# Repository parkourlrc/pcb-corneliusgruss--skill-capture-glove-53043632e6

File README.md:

# Skill-Capture Glove

*A worn skill-capture system — end-to-end hardware, SLAM, and policy. Solo, four months.*

An independent reimplementation of [Sunday Robotics'](https://sunday.ai/) Skill Capture Glove form factor, built solo from January through April 2026 as the final project for ME740 (Vision, Robotics, and Planning, Boston University). The hardware shown above is the V3 build with on-glove OV9782 stereo cameras; the production pose pipeline uses an externally-mounted GoPro Hero 10 plus [UMI's](https://umi-gripper.github.io/) monocular SLAM stack with [Hierarchical-Localization](https://github.com/cvg/Hierarchical-Localization) replacing ORB-SLAM3.

The repository contains every layer of the system: PCB design, firmware, capture pipeline, SLAM, alignment, and an ACT policy trained on 182 mug-on-coaster demonstrations.

<p align="center"><i>One demonstration: pick the mug, place it on the coaster (~15 s).</i></p>

---

## What's in here

| Layer | What it does | Where |
|---|---|---|
| **Hardware** | Custom DAQ PCB (KiCad), four MLX90393 Hall sensor PCBs, V3 glove CAD | [`hardware/`](hardware/) |
| **Firmware** | STM32G431 — bit-bang I²C, USB CDC, sensor scheduling | [`firmware/stm32_daq/`](firmware/stm32_daq/) |
| **Capture** | Master-tape recorder + GoPro offload + per-demo ingest | [`software/glove/capture/`](software/), [`software/glove/process/`](software/) |
| **SLAM** | HLoc (SuperPoint + LightGlue + NetVLAD + COLMAP) + pose-graph smoother + Gaussian σ=5 | [`software/glove/process/hloc/`](software/) |
| **Align** | Trajectory + proprioception → training-ready `episode.parquet` | [`software/glove/process/align.py`](software/) |
| **Policy** | ACT (Zhao et al. 2023) — DINOv2 frozen backbone, 23-D obs, 21-D action | [`software/glove/policy/`](software/) |
| **Review dashboard** | Browse-only FastAPI UI for triaging captured demos against quality metrics | [`software/glove/dashboard/`](software/glove/dashboard/) |
| **Paper** | ME740 final report | [`paper/me740_report.pdf`](paper/me740_report.pdf) |

---

## Pipeline

Five command-line stages, each operating on session directories with a stable schema:

```bash
python -m glove.capture record                     # continuous DAQ writer
python -m glove.capture offload                    # SD card → disk
python -m glove.process ingest --mp4 <file> ...    # MP4 + master tape → session dir
python -m glove.process build-model <map-session>  # SfM + HLoc map (run once per workspace)
python -m glove.process detect-aruco <map>         # tag detection
python -m glove.process calibrate-tag <map>        # gravity-align world frame
python -m glove.process localize <demo> --map <m>  # per-frame pose against the map
python -m glove.process align <demo>               # → episode.parquet
python -m glove.dashboard --data-dir data/sessions # browse + review demos at localhost:8000
```

See [`docs/reproduce.md`](docs/reproduce.md) for end-to-end reproduction commands. The full system architecture is documented in §3 of the [paper](paper/me740_report.pdf).

---

## Review dashboard

A FastAPI browse-only UI for triaging captured demonstrations. Surfaces per-demo trajectory-quality metrics (local-straightness, high-frequency RMS, pose-jump max) on a scrubbable timeline alongside the GoPro video. This is the tool that caught 23% of the unfiltered demonstration set as silent SLAM pose-graph re-anchoring artifacts during the label audit.

---

## Headline results

- **SLAM proven against ground truth.** A controlled validation against a Kalibr 6×6 AprilGrid places the production HLoc + σ=5 stack within **0.2 mm** of the absolute camera + PnP physical noise floor on static no-cup frames (HLoc 8.3 mm p95 vs. AprilGrid 8.1 mm p95). Further improvement bounded to capture-side hardware.
- **Per-joint Hall force sensing.** A controlled scale-press experiment recovers **+1.29 counts/g (R² = 0.64)** on the compliant 3F PIP joint — force enters the policy as a designed-in byproduct of the PIP-slit axial compliance, not via a calibrated load cell.
- **ACT policy on 182 demonstrations.** The production checkpoint reaches **28.8 mm position L1, 6.31° rotation L1, and 736 LSB Hall L1** on a held-out validation set against the HLoc + σ=5 ground truth — roughly 3.5× the truth-source's own measurement floor. A label-quality audit — driven by the [browse-only review dashboard](software/glove/dashboard/) shipped alongside the pipeline — excluded 23% of the unfiltered demonstration set as silent SLAM pose-graph re-anchoring artifacts before retraining.

  <p align="center"><i>Production policy predicting the next action chunk on a held-out demonstration. Predicted Hall traces (right panel) track the squeeze cycle through the grasp event.</i></p>

- **Eight-backend SLAM pivot chain.** DROID → COLMAP → custom stereo SIFT → OKVIS2 → custom GTSAM v1/v2/v3 → ORB-SLAM3 → HLoc + smoother. Each fork accepted what the evidence said rather than tuning a stack already at its diagnosed limit. Full chain documented in Sec. 5 of the paper.

---

## Built with

- [UMI](https://umi-gripper.github.io/) — Cheng Chi et al. 2024. Source of the Hero 10 + ORB-SLAM3 + Docker stack the production pipeline forked from.
- [Hierarchical-Localization (HLoc)](https://github.com/cvg/Hierarchical-Localization) — Sarlin et al. 2019. Production SLAM stack.
- [SuperPoint](https://github.com/magicleap/SuperPointPretrainedNetwork), [LightGlue](https://github.com/cvg/LightGlue), [NetVLAD](https://github.com/Relja/netvlad), [COLMAP](https://github.com/colmap/colmap)
- [ACT](https://github.com/tonyzhaozh/act) — Zhao et al. 2023. Policy architecture.
- [DINOv2](https://github.com/facebookresearch/dinov2) — frozen ViT-S/14 visual backbone.
- [GoPro Labs UTC precision-time QR](https://gopro.github.io/labs/control/precisiontime_utc/) — for ms-accurate camera-to-DAQ time sync.

---

## Hardware overview

- **Glove V3.** Two finger assemblies (single index + three-finger), four PIP and four MCP joints with 3 × 2 mm diametric magnets, fingertip caps, PIP axial-slit compliance.
- **DAQ PCB.** STM32G431 + TCA9548A I²C mux + QMI8658C IMU + 4 × MLX90393 Hall + 2 × VL53L1X ToF + USB CDC. Four-layer PCB, KiCad, manufactured by JLCPCB.
- **Cameras.** OV9782 stereo (on-glove, V3 build) + GoPro Hero 10 + MaxLens Mod 1.0 (155° fisheye, externally mounted, used for production SLAM).

The on-glove OV9782 stereo cameras shown in the hero image were the original SLAM sensors. The current pose pipeline uses the externally-mounted GoPro because OV9782 stereo VIO did not converge on the assembled glove (finger occlusion + USB bandwidth). Whether the HLoc stack would close the loop on the OV9782 cameras given a V4 USB and lens revision is an open question.

---

## Paper

**[A Worn Skill-Capture System: End-to-End Hardware, SLAM, and Policy](paper/me740_report.pdf)**
Cornelius Gruss · ME740 (Vision, Robotics, and Planning) · Boston University · 2026

---

## License

[MIT](LICENSE) — use, modify, and redistribute freely.

## Acknowledgments

Form factor inspired by [Sunday Robotics'](https://sunday.ai/) Skill Capture Glove. SLAM pipeline forked from [UMI](https://umi-gripper.github.io/). Policy architecture adapted from [ALOHA / ACT](https://github.com/tonyzhaozh/act). Built as the final project for ME740 (Spring 2026, Boston University) under Prof. John Baillieul.

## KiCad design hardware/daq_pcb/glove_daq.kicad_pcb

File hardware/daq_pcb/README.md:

# DAQ PCB

Sensor aggregation and timing backbone for the glove. Streams synchronized proprioceptive data over USB-CDC to the host.

| | |
|---|---|
| **MCU** | STM32G431CBT6 (LQFP-48, 170 MHz, crystal-less USB via CRS) |
| **IMU** | QMI8658C — 6-DoF, I²C @ 0x6A |
| **I²C mux** | TCA9548A @ 0x70 — 6 sensor channels |
| **Sensors (off-board)** | 4× MLX90393 Hall (joint), 2× VL53L1X ToF |
| **Camera sync** | TIM1 hardware PWM, 30 Hz, 3.3 V on JST-SH |
| **Host link** | USB-C, CDC-ACM @ 12 Mbps |
| **Stack-up** | 2-layer FR4, 1.6 mm, HASL |
| **Form factor** | ~40 × 30 mm |
| **Fabricator** | JLCPCB (PCB + economic SMT assembly) |

## Files

| Path | What |
|---|---|
| `glove_daq.kicad_pro` / `.kicad_pcb` / `.kicad_sch` | KiCad 7 project |
| `glove_daq.pdf` | Schematic export |
| `glove_daq.step` | 3D model (board + components) |
| `BOM.xlsx` | Bill of materials |
| `JLCPCB_BOM.csv` | JLC-formatted BOM for SMT assembly |
| `mfr/glove_daq.zip` | Gerber + drill bundle (drop into JLCPCB upload) |
| `mfr/glove_daq-all-pos.csv` | Component positions for SMT assembly |
| `aruco/` | ArUco marker footprints + reference renders |

## Manufacturing

Upload `mfr/glove_daq.zip` (gerbers + drill) and `mfr/glove_daq-all-pos.csv` (positions) plus `JLCPCB_BOM.csv` to JLCPCB's PCBA flow. SWD header (J2, 1×4 2.54 mm THT) is hand-soldered.

## I²C mux assignment

| Channel | Sensor | Address |
|---|---|---|
| CH0 | VL53L1X ToF (bottom) | 0x29 |
| CH1 | MLX90393 Hall (3F MCP) | 0x0C |
| CH2 | MLX90393 Hall (Index PIP) | 0x0C |
| CH3 | MLX90393 Hall (3F PIP) | 0x0C |
| CH4 | MLX90393 Hall (Index MCP) | 0x0C |
| CH5 | VL53L1X ToF (top) | 0x29 |

## USB packet format (40 bytes, type 0x02 @ 30 Hz)

| Offset | Size | Field |
|---|---|---|
| 0 | 1 | Packet type (0x02) |
| 1 | 4 | Timestamp (ns) |
| 5 | 24 | 4× Hall (Bx, By, Bz int16) |
| 29 | 4 | 2× ToF (mm, int16; −1 = no reading) |
| 33 | 4 | Sync pulse timestamp (µs of last camera trigger) |
| 37 | 1 | Status flags |
| 38 | 2 | Sync sequence counter |

A separate type-0x01 packet streams raw IMU at ~680 Hz.

## Design notes

- **Crystal-less USB.** STM32G4's Clock Recovery System trims HSI48 against USB SOF — eliminates the external crystal, removes a failure mode, frees board area. Init order matters: enable HSI48 → enable CRS → select HSI48 as USB clock → init USB peripheral.
- **No battery, no SD card.** Tethered operation is required for video offload anyway, so battery + power-path management would add ~10 components for no functional gain. SPI2 (PB12–PB15) is left free for future logging.
- **JST-SH (1.0 mm) connectors.** Same physical footprint as Qwiic / STEMMA QT, half the area of JST-PH. SMD right-angle variants keep the board flat for IMU rigidity.
- **IMU substitution.** JLCPCB's "ICM-42688-PC" extended part (C2839811) is a pin-compatible **clone** — the actual silicon is QMI8658C, with a different register map and I²C-only operation. Firmware bit-bangs I²C on the SPI1 pads (PA5/SCK→SCL, PA7/MOSI→SDA, PA4/CS held HIGH for I²C mode). Lesson: never use JLC "extended" parts for specialty ICs without verifying WHO_AM_I.
- **Bit-bang I²C everywhere.** STM32 HAL's I²C peripheral hung intermittently under sensor load (mux switching + clock stretching). Bit-banging is slower but deterministic.

## License

MIT — see repository root.

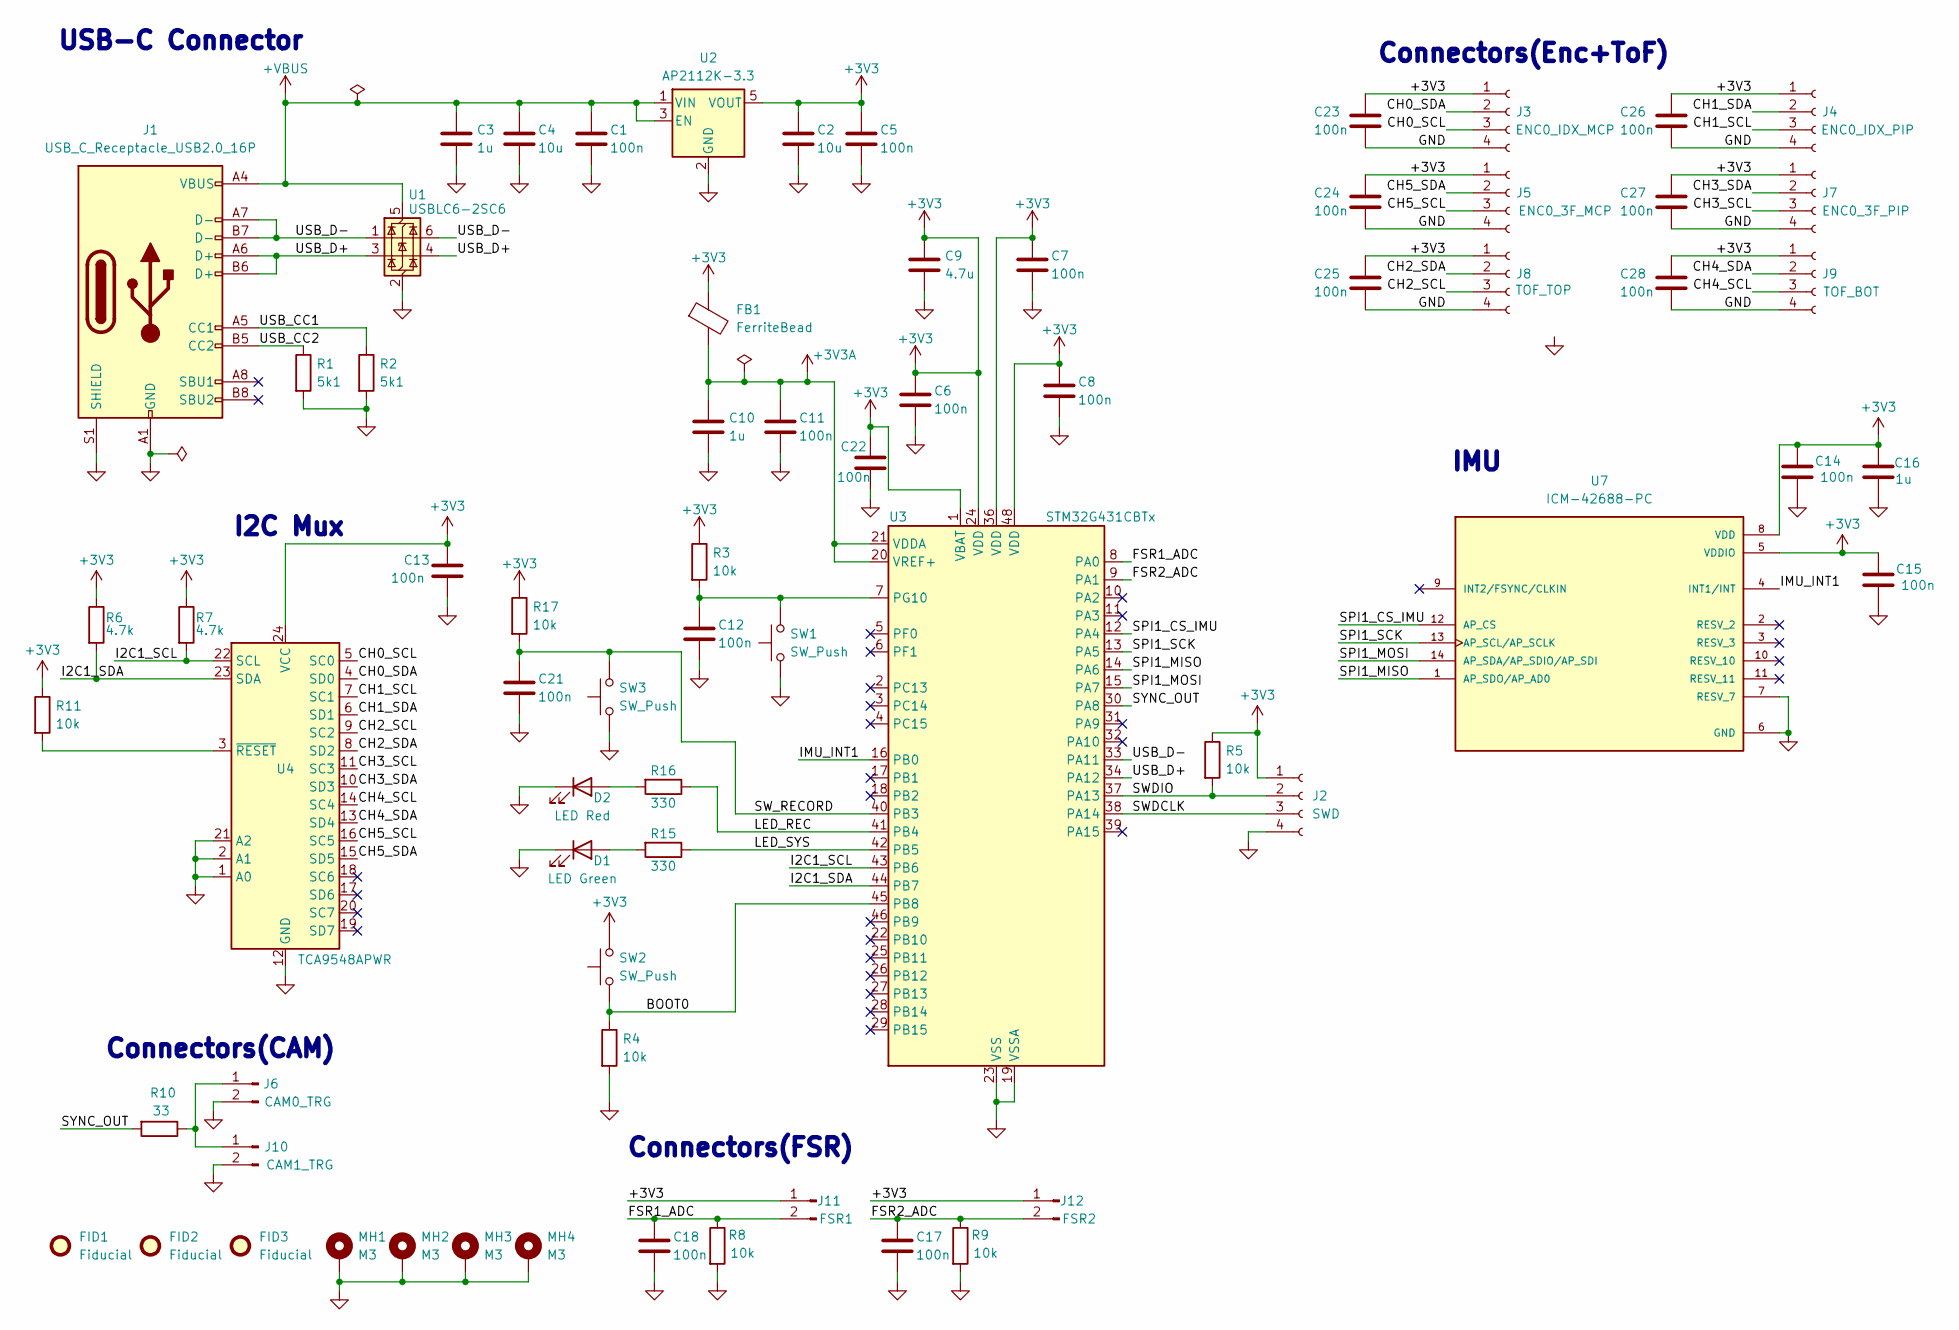
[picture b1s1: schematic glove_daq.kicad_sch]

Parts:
C1, C5, C6, C7, C8, C11, C12, C13, C14, C15, C17, C18, C21, C22, C23, C24, C25, C26, C27, C28: 100n; C_0402_1005Metric; LCSC C307331
C2, C4: 10u; C_0402_1005Metric; LCSC C15525
C3, C10, C16: 1u; C_0402_1005Metric; LCSC C52923
C9: 4.7u; C_0402_1005Metric; LCSC C23733
D1: LED Green; LED_0805_2012Metric; LCSC C2297
D2: LED Red; LED_0603_1608Metric; LCSC C2286
FB1: FerriteBead; L_0603_1608Metric; LCSC C1002
FID1, FID2, FID3: Fiducial; Fiducial_1mm_Mask2mm
J1: USB_C_Receptacle_USB2.0_16P; USB_C_Receptacle_GCT_USB4105-xx-A_16P_TopMnt_Horizontal; LCSC C3020560
J2: SWD; JST_SH_BM04B-SRSS-TB_1x04-1MP_P1.00mm_Vertical; LCSC C160390
J3: ENC0_IDX_MCP; JST_SH_SM04B-SRSS-TB_1x04-1MP_P1.00mm_Horizontal; LCSC C160404
J4: ENC0_IDX_PIP; JST_SH_SM04B-SRSS-TB_1x04-1MP_P1.00mm_Horizontal; LCSC C160404
J5: ENC0_3F_MCP; JST_SH_SM04B-SRSS-TB_1x04-1MP_P1.00mm_Horizontal; LCSC C160404
J6: CAM0_TRG; JST_SH_SM02B-SRSS-TB_1x02-1MP_P1.00mm_Horizontal; LCSC C160402
J7: ENC0_3F_PIP; JST_SH_SM04B-SRSS-TB_1x04-1MP_P1.00mm_Horizontal; LCSC C160404
J8: TOF_TOP; JST_SH_SM04B-SRSS-TB_1x04-1MP_P1.00mm_Horizontal; LCSC C160404
J9: TOF_BOT; JST_SH_SM04B-SRSS-TB_1x04-1MP_P1.00mm_Horizontal; LCSC C160404
J10: CAM1_TRG; JST_SH_SM02B-SRSS-TB_1x02-1MP_P1.00mm_Horizontal; LCSC C160402
J11: FSR1; JST_SH_SM02B-SRSS-TB_1x02-1MP_P1.00mm_Horizontal; LCSC C160402
J12: FSR2; JST_SH_SM02B-SRSS-TB_1x02-1MP_P1.00mm_Horizontal; LCSC C160402
MH1, MH2, MH3, MH4: M3; MountingHole_3.2mm_M3_Pad
R1, R2: 5k1; R_0402_1005Metric; LCSC C25905
R3, R4, R5, R8, R9, R11, R17: 10k; R_0402_1005Metric; LCSC C25744
R6, R7: 4.7k; R_0402_1005Metric; LCSC C25900
R10: 33; R_0402_1005Metric; LCSC C25105
R15, R16: 330; R_0402_1005Metric; LCSC C25104
SW1, SW2, SW3: SW_Push; SW_SPST_TS-1088-xR025; LCSC C720477
U1: USBLC6-2SC6; SOT-23-6; LCSC C7519
U2: AP2112K-3.3; SOT-23-5; LCSC C51118
U3: STM32G431CBTx; LQFP-48_7x7mm_P0.5mm; LCSC C529355
U4: TCA9548APWR; TSSOP-24_4.4x7.8mm_P0.65mm; LCSC C130026
U7: ICM-42688-PC; PQFN50P300X250X97-14N; PARTREV 1.2; LCSC C48586483

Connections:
+3V3: C2.1, C5.1, C6.1, C7.1, C8.1, C9.1, C13.1, C14.1, C15.1, C16.1, C22.1, C23.1, C24.1, C25.1, C26.1, C27.1, C28.1, FB1.1, J2.1, J3.1, J4.1, J5.1, J7.1, J8.1, J9.1, J11.1, J12.1, R3.1, R5.1, R6.1, R7.1, R11.1, R17.1, SW2.2, U2.5 (VOUT), U3.1 (VBAT), U3.24 (VDD), U3.36 (VDD), U3.48 (VDD), U4.24 (VCC), U7.5 (VDDIO), U7.8 (VDD)
+3V3A: C10.1, C11.1, FB1.2, U3.20 (VREF+), U3.21 (VDDA)
+VBUS: C1.1, C3.1, C4.1, J1.A4 (VBUS), J1.A9 (VBUS), J1.B4 (VBUS), J1.B9 (VBUS), U1.5 (VBUS), U2.1 (VIN), U2.3 (EN)
/BOOT0: R4.1, SW2.1, U3.45 (PB8)
/CH0_SCL: J3.3, U4.5 (SC0)
/CH0_SDA: J3.2, U4.4 (SD0)
/CH1_SCL: J4.3, U4.7 (SC1)
/CH1_SDA: J4.2, U4.6 (SD1)
/CH2_SCL: J8.3, U4.9 (SC2)
/CH2_SDA: J8.2, U4.8 (SD2)
/CH3_SCL: J7.3, U4.11 (SC3)
/CH3_SDA: J7.2, U4.10 (SD3)
/CH4_SCL: J9.3, U4.14 (SC4)
/CH4_SDA: J9.2, U4.13 (SD4)
/CH5_SCL: J5.3, U4.16 (SC5)
/CH5_SDA: J5.2, U4.15 (SD5)
/FSR1_ADC: C18.1, J11.2, R8.1, U3.8 (PA0)
/FSR2_ADC: C17.1, J12.2, R9.1, U3.9 (PA1)
/I2C1_SCL: R7.2, U3.43 (PB6), U4.22 (SCL)
/I2C1_SDA: R6.2, U3.44 (PB7), U4.23 (SDA)
/IMU_INT1: U3.16 (PB0), U7.4 (INT1/INT)
/LED_REC: R16.1, U3.41 (PB4)
/LED_SYS: R15.1, U3.42 (PB5)
/SPI1_CS_IMU: U3.12 (PA4), U7.12 (AP_CS)
/SPI1_MISO: U3.14 (PA6), U7.1 (AP_SDO/AP_AD0)
/SPI1_MOSI: U3.15 (PA7), U7.14 (AP_SDA/AP_SDIO/AP_SDI)
/SPI1_SCK: U3.13 (PA5), U7.13 (AP_SCL/AP_SCLK)
/SWDCLK: J2.3, U3.38 (PA14)
/SWDIO: J2.2, R5.2, U3.37 (PA13)
/SW_RECORD: C21.1, R17.2, SW3.2, U3.40 (PB3)
/SYNC_OUT: R10.2, U3.30 (PA8)
/USB_CC1: J1.A5 (CC1), R2.1
/USB_CC2: J1.B5 (CC2), R1.1
/USB_D+: J1.A6 (D+), J1.B6 (D+), U1.3 (I/O2), U1.4 (I/O2), U3.34 (PA12)
/USB_D-: J1.A7 (D-), J1.B7 (D-), U1.1 (I/O1), U1.6 (I/O1), U3.33 (PA11)
GND: C1.2, C2.2, C3.2, C4.2, C5.2, C6.2, C7.2, C8.2, C9.2, C10.2, C11.2, C12.2, C13.2, C14.2, C15.2, C16.2, C17.2, C18.2, C21.2, C22.2, C23.2, C24.2, C25.2, C26.2, C27.2, C28.2, D1.1 (K), D2.1 (K), J1.A1 (GND), J1.A12 (GND), J1.B1 (GND), J1.B12 (GND), J1.S1 (SHIELD), J2.4, J3.4, J4.4, J5.4, J6.2, J7.4, J8.4, J9.4, J10.2, MH1.1, MH2.1, MH3.1, MH4.1, R1.2, R2.2, R4.2, R8.2, R9.2, SW1.1, SW3.1, U1.2 (GND), U2.2 (GND), U3.19 (VSSA), U3.23 (VSS), U3.35 (VSS), U3.47 (VSS), U4.1 (A0), U4.2 (A1), U4.12 (GND), U4.21 (A2), U7.6 (GND), U7.7 (RESV_7)
unnamed: D1.2 (A), R15.2
unnamed: D2.2 (A), R16.2
unnamed: J6.1, J10.1, R10.1
unnamed: C12.1, R3.2, SW1.2, U3.7 (PG10)
unnamed: R11.2, U4.3 (~RESET)

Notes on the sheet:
USB-C Connector
Connectors(CAM)
Connectors(FSR)
IMU
I2C Mux
Connectors(Enc+ToF)

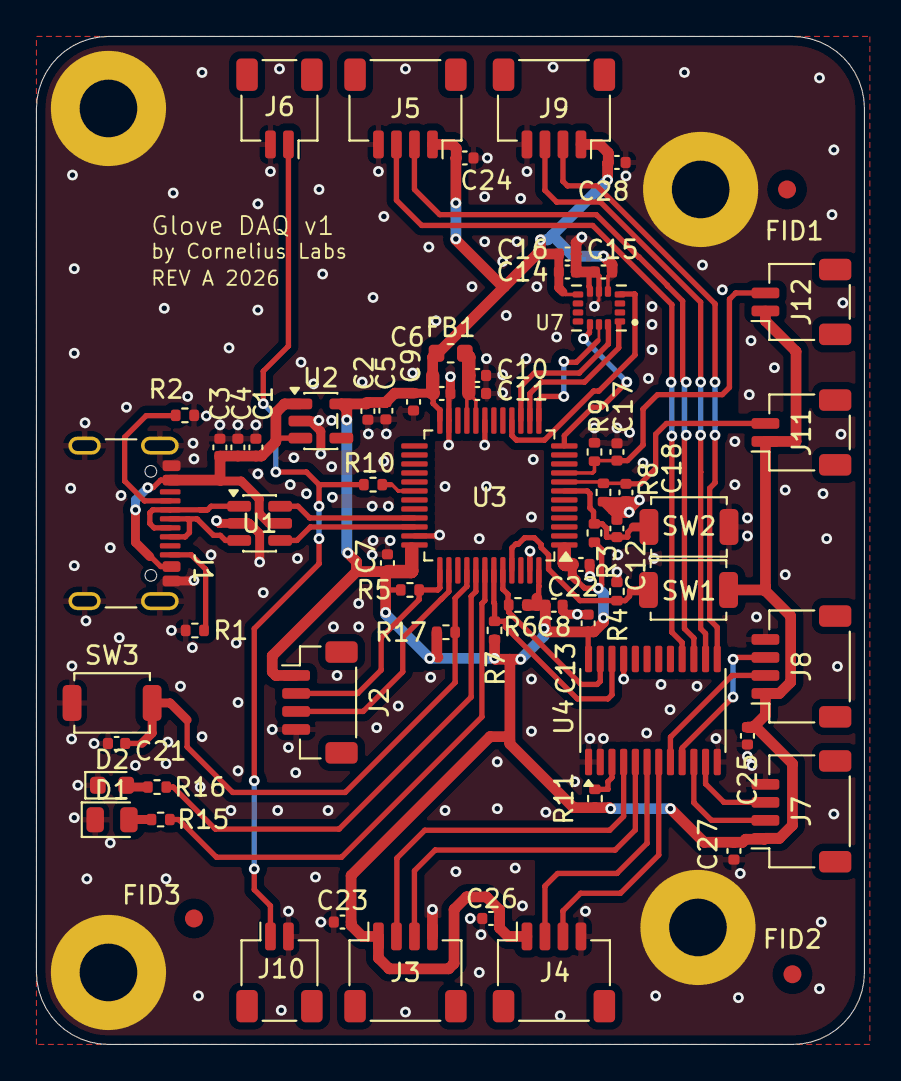
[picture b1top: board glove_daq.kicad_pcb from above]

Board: 2 copper layers, 46.0 x 56.0 mm, 70 parts (0 on the bottom side), 41 nets.

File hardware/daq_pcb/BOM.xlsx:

Ref | Value | Description | Package | LCSC Part # | JLCPCB Type | Group | Qty | Notes
USB-C + Power
J1 | USB_C_16P | USB-C 2.0 Receptacle 16-pin | SMD | C165948 | Basic |  | 1 | HRO TYPE-C-31-M-12
U1 | USBLC6-2SC6 | USB ESD Protection | SOT-23-6 | C7519 | Basic |  | 1
R1 | 5.1kΩ | CC1 pull-down | 0402 | C25905 | Basic |  | 1
R2 | 5.1kΩ | CC2 pull-down | 0402 | C25905 | Basic |  | 1
C1 | 100nF | VBUS HF decoupling | 0402 | C307331 | Basic |  | 1 | 50V rated
C3 | 1µF | VBUS mid-freq decoupling | 0402 | C52923 | Basic |  | 1
C4 | 10µF | VBUS bulk decoupling | 0402 | C15525 | Basic |  | 1 | 16V rated
U2 | AP2112K-3.3 | 3.3V LDO 600mA | SOT-23-5 | C51118 | Basic |  | 1
C2 | 10µF | LDO output bulk | 0402 | C15525 | Basic |  | 1
C5 | 100nF | LDO output HF | 0402 | C307331 | Basic |  | 1
STM32G431 MCU
U3 | STM32G431CBT6 | ARM Cortex-M4 MCU 170MHz | LQFP-48 | C529331 | Extended |  | 1 | Crystal-less USB via CRS
C6 | 100nF | VDD decoupling (pin 24) | 0402 | C307331 | Basic |  | 1
C7 | 100nF | VDD decoupling (pin 36) | 0402 | C307331 | Basic |  | 1
C8 | 100nF | VDD decoupling (pin 48) | 0402 | C307331 | Basic |  | 1
C9 | 4.7µF | VDD bulk | 0402 | C23733 | Basic |  | 1
C22 | 100nF | VBAT decoupling | 0402 | C307331 | Basic |  | 1
FB1 | 600Ω@100MHz | VDDA ferrite bead filter | 0402 | C281128 | Basic |  | 1
C10 | 1µF | VDDA decoupling | 0402 | C52923 | Basic |  | 1
C11 | 100nF | VDDA HF decoupling | 0402 | C307331 | Basic |  | 1
R17 | 10kΩ | NRST pull-up | 0402 | C25744 | Basic |  | 1
C12 | 100nF | NRST filter cap | 0402 | C307331 | Basic |  | 1
SW1 | RESET | Tactile push button | 6x6mm SMD | C318884 | Basic |  | 1
R4 | 10kΩ | BOOT0 pull-down | 0402 | C25744 | Basic |  | 1
SW2 | BOOT0 | Tactile push button | 6x6mm SMD | C318884 | Basic |  | 1
J2 | SWD Header | 1x4 pin header 2.54mm | THT | C2337 | Basic |  | 1
R5 | 10kΩ | SWDIO pull-up | 0402 | C25744 | Basic |  | 1
Camera Sync
R10 | 33Ω | SYNC_OUT series damping | 0402 | C25105 | Basic |  | 1
J6 | CAM0_TRG | JST-PH 2-pin right-angle | SMD | C131337 | Basic |  | 1
J10 | CAM1_TRG | JST-PH 2-pin right-angle | SMD | C131337 | Basic |  | 1
I2C Mux + Sensors
U4 | TCA9548APWR | I2C 8-channel multiplexer | TSSOP-24 | C130026 | Basic |  | 1
C13 | 100nF | Mux VCC decoupling | 0402 | C307331 | Basic |  | 1
R11 | 10kΩ | Mux RESET pull-up | 0402 | C25744 | Basic |  | 1
R6 | 4.7kΩ | I2C SCL pull-up | 0402 | C25900 | Basic |  | 1
R7 | 4.7kΩ | I2C SDA pull-up | 0402 | C25900 | Basic |  | 1
J3 | ENC0_IDX_MCP | JST-PH 4-pin right-angle | SMD | C131337 | Basic |  | 1 | Encoder CH0
J4 | ENC0_IDX_PIP | JST-PH 4-pin right-angle | SMD | C131337 | Basic |  | 1 | Encoder CH1
J5 | ENC0_3F_MCP | JST-PH 4-pin right-angle | SMD | C131337 | Basic |  | 1 | Encoder CH2
J7 | ENC0_3F_PIP | JST-PH 4-pin right-angle | SMD | C131337 | Basic |  | 1 | Encoder CH3
J8 | TOF_TOP | JST-PH 4-pin right-angle | SMD | C131337 | Basic |  | 1 | ToF CH4
J9 | TOF_BOT | JST-PH 4-pin right-angle | SMD | C131337 | Basic |  | 1 | ToF CH5
C_J3 | 100nF | ENC0_IDX_MCP connector decoupling | 0402 | C307331 | Basic |  | 1
C_J4 | 100nF | ENC0_IDX_PIP connector decoupling | 0402 | C307331 | Basic |  | 1
C_J5 | 100nF | ENC0_3F_MCP connector decoupling | 0402 | C307331 | Basic |  | 1
C_J7 | 100nF | ENC0_3F_PIP connector decoupling | 0402 | C307331 | Basic |  | 1
C_J8 | 100nF | TOF_TOP connector decoupling | 0402 | C307331 | Basic |  | 1
C_J9 | 100nF | TOF_BOT connector decoupling | 0402 | C307331 | Basic |  | 1
IMU
U7 | ICM-42688-P | 6-axis IMU (gyro+accel) | LGA-14 | C2839811 | Extended |  | 1 | Check stock — ICM-42670-P as backup
C14 | 100nF | IMU VDDIO decoupling | 0402 | C307331 | Basic |  | 1
C15 | 100nF | IMU VDD decoupling | 0402 | C307331 | Basic |  | 1
C16 | 1µF | IMU VDD bulk | 0402 | C52923 | Basic |  | 1
FSR Force Sensing
J11 | FSR1 | JST-PH 2-pin right-angle | SMD | C131337 | Basic |  | 1
J12 | FSR2 | JST-PH 2-pin right-angle | SMD | C131337 | Basic |  | 1
R8 | 10kΩ | FSR1 pull-down | 0402 | C25744 | Basic |  | 1
R9 | 10kΩ | FSR2 pull-down | 0402 | C25744 | Basic |  | 1
C17 | 100nF | FSR1 RC filter | 0402 | C307331 | Basic |  | 1
C18 | 100nF | FSR2 RC filter | 0402 | C307331 | Basic |  | 1
SD Card
J13 | Micro_SD | MicroSD card socket push-push | SMD | C91145 | Basic |  | 1 | HYC80-TF09-375 or equiv
R12 | 10kΩ | SD DAT2 pull-up | 0402 | C25744 | Basic |  | 1
R13 | 10kΩ | SD DAT1 pull-up | 0402 | C25744 | Basic |  | 1
R14 | 10kΩ | SD Card Detect pull-up | 0402 | C25744 | Basic |  | 1
C19 | 10µF | SD VDD bulk | 0402 | C15525 | Basic |  | 1
C20 | 100nF | SD VDD HF | 0402 | C307331 | Basic |  | 1
User Interface
D1 | Green LED | System status LED | 0402 | C2297 | Basic |  | 1
D2 | Red LED | Recording status LED | 0402 | C2286 | Basic |  | 1
R15 | 330Ω | Green LED current limit | 0402 | C25104 | Basic |  | 1
R16 | 330Ω | Red LED current limit | 0402 | C25104 | Basic |  | 1
SW3 | RECORD | Tactile push button | 6x6mm SMD | C318884 | Basic |  | 1
R3 | 10kΩ | Record button pull-up | 0402 | C25744 | Basic |  | 1
C21 | 100nF | Record button debounce | 0402 | C307331 | Basic |  | 1
Mechanical
MH1-4 | M3 | Mounting hole pad | M3 THT | — | — |  | 4 | Connect pad to GND
FID1-3 | Fiducial | 1mm copper, 2mm mask opening | Fiducial | — | — |  | 3 | JLCPCB pick-and-place alignment
BOM Summary
Total Unique Parts | ~30
Total Component Count | ~72
JLCPCB Basic Parts | ~28
JLCPCB Extended Parts | 2 (STM32G431, ICM-42688-P)
Passive Size | 0402 (all)
Board Layers | 2 (recommended)

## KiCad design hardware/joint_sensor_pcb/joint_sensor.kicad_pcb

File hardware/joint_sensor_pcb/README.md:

# Joint sensor PCB

Micro-PCB that mounts on each finger flexure to capture joint angle and axial compliance from a single diametric magnet.

| | |
|---|---|
| **Sensor** | Melexis MLX90393 (3-axis Hall, QFN-16) |
| **Interface** | I²C @ 0x0C (routed through DAQ board's TCA9548A mux) |
| **Power** | 3.3 V from DAQ board |
| **Form factor** | 15 × 20 mm, 2-layer FR4 |
| **Connector** | JST-SH 4-pin right-angle (3V3 / GND / SDA / SCL) |
| **Magnet** | 3 × 2 mm N52 diametric, mounted in finger CAD |
| **Quantity per glove** | 4 (Index MCP + PIP, three-finger MCP + PIP) |

## Files

| Path | What |
|---|---|
| `joint_sensor.kicad_pro` / `.kicad_pcb` / `.kicad_sch` | KiCad 7 project |
| `joint_sensor.step` | 3D model |
| `mfr/joint_sensor.zip` | Gerber + drill bundle |
| `mfr/joint_sensor-all-pos.csv` | Component positions for SMT |

## What it produces

Three int16 readings per sensor (Bx, By, Bz). The host derives:

- **Angle** from `atan2(By, Bx)` — continuous through wrap, no discontinuity.
- **Force** from `Bz` magnitude — the axial-slit PIP flexure deflects under load, changing the magnet's standoff and shifting Bz. Calibrated against a precision scale: **+1.29 counts/g, R² = 0.64** on the compliant 3F PIP joint (range ~300–1300 g).

The policy receives raw `(Bx, By, Bz)` per sensor — no on-host atan2 — so the network sees angle and force as a single 12-D continuous representation.

## Layout rules

1. **Sensor on the centerline**, aligned with the hinge-pin axis in CAD.
2. **No copper under the chip** — solid pours induce eddy currents under a moving magnet that bias the field reading. KiCad keep-out zone, ~5 × 5 mm, both layers.
3. **15 mm lever arm** between the sensor center and the M2 mounting holes. The flexure deflection that gives Bz its force-sensing range scales with this distance.

## License

MIT — see repository root.

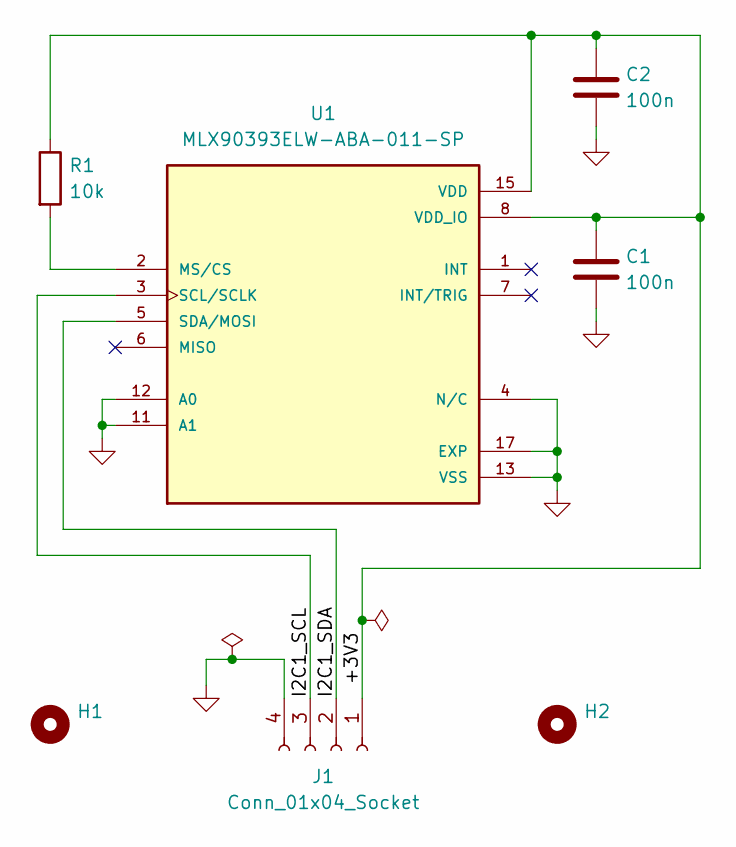
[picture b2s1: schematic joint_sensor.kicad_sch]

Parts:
C1, C2: 100n; C_0402_1005Metric; LCSC C307331
H1, H2: MountingHole; MountingHole_2.2mm_M2_DIN965
J1: Conn_01x04_Socket; JST_SH_SM04B-SRSS-TB_1x04-1MP_P1.00mm_Horizontal; LCSC C160404
R1: 10k; R_0402_1005Metric; LCSC C25744
U1: MLX90393ELW-ABA-011-SP; QFN50P300X300X100-17N; PARTREV 010; LCSC C2649492

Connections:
/+3V3: C1.1, C2.1, J1.1, R1.1, U1.8 (VDD_IO), U1.15 (VDD)
/I2C1_SCL: J1.3, U1.3 (SCL/SCLK)
/I2C1_SDA: J1.2, U1.5 (SDA/MOSI)
GND: C1.2, C2.2, J1.4, U1.4 (N/C), U1.9 (N/C), U1.10 (N/C), U1.11 (A1), U1.12 (A0), U1.13 (VSS), U1.14 (N/C), U1.16 (N/C), U1.17 (EXP)
unnamed: R1.2, U1.2 (MS/CS)

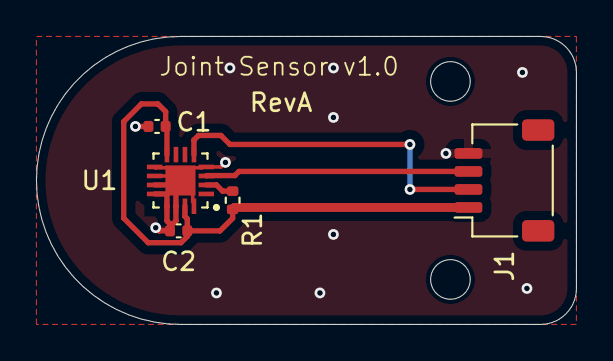
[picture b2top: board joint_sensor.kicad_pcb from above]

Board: 2 copper layers, 30.0 x 16.0 mm, 7 parts (0 on the bottom side), 5 nets.

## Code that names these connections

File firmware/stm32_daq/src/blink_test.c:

/**
 * blink_test.c — IMU diagnostic: tries SPI then I2C on same pins
 */

#include "stm32g4xx_hal.h"
#include "config.h"
#include "tusb.h"
#include <stdio.h>
#include <string.h>

extern void system_clock_init(void);

static void led_gpio_init(void)
{
    __HAL_RCC_GPIOB_CLK_ENABLE();
    GPIO_InitTypeDef gpio = {0};
    gpio.Pin = LED_SYS_PIN | LED_REC_PIN;
    gpio.Mode = GPIO_MODE_OUTPUT_PP;
    gpio.Pull = GPIO_NOPULL;
    gpio.Speed = GPIO_SPEED_FREQ_LOW;
    HAL_GPIO_Init(LED_SYS_PORT, &gpio);
}

/* USB */
void USB_HP_IRQHandler(void)    { tud_int_handler(0); }
void USB_LP_IRQHandler(void)    { tud_int_handler(0); }
void USBWakeUp_IRQHandler(void) { tud_int_handler(0); }
void tud_mount_cb(void) {}
void tud_umount_cb(void) {}
void tud_suspend_cb(bool rw) { (void)rw; }
void tud_resume_cb(void) {}
void tud_cdc_line_state_cb(uint8_t i, bool d, bool r) { (void)i;(void)d;(void)r; }
void tud_cdc_rx_cb(uint8_t i) { (void)i; }

static void usb_init(void)
{
    __HAL_RCC_PWR_CLK_ENABLE();
    PWR->CR3 |= PWR_CR3_UCPD_DBDIS;
    __HAL_RCC_USB_CLK_ENABLE();
    __HAL_RCC_GPIOA_CLK_ENABLE();
    HAL_NVIC_SetPriority(USB_HP_IRQn, 3, 0);
    HAL_NVIC_SetPriority(USB_LP_IRQn, 3, 0);
    HAL_NVIC_SetPriority(USBWakeUp_IRQn, 3, 0);
    tusb_init();
}

static char pbuf[128];
static void cdc_print(const char *s)
{
    if (!tud_cdc_connected()) return;
    tud_cdc_write(s, strlen(s));
    tud_cdc_write_flush();
    /* Give USB time to drain */
    for (int i = 0; i < 10; i++) { tud_task(); HAL_Delay(1); }
}

/* ── Bit-bang I2C on PA5(SCL) + PA7(SDA), PA4(CS) held high ──────── */

#define PIN_CS   GPIO_PIN_4
#define PIN_SCL  GPIO_PIN_5
#define PIN_SDA  GPIO_PIN_7

static void i2c_delay(void) { for (volatile int i = 0; i < 40; i++) {} }

static void i2c_gpio_init(void)
{
    __HAL_RCC_GPIOA_CLK_ENABLE();
    GPIO_InitTypeDef gpio = {0};

    /* CS high = I2C mode on ICM-42688 */
    gpio.Pin = PIN_CS;
    gpio.Mode = GPIO_MODE_OUTPUT_PP;
    gpio.Pull = GPIO_NOPULL;
    gpio.Speed = GPIO_SPEED_FREQ_HIGH;
    HAL_GPIO_Init(GPIOA, &gpio);
    GPIOA->BSRR = PIN_CS;  /* CS HIGH */

    /* SCL + SDA as open-drain with pull-ups */
    gpio.Pin = PIN_SCL | PIN_SDA;
    gpio.Mode = GPIO_MODE_OUTPUT_OD;
    gpio.Pull = GPIO_PULLUP;
    HAL_GPIO_Init(GPIOA, &gpio);

    GPIOA->BSRR = PIN_SCL;
    GPIOA->BSRR = PIN_SDA;
    HAL_Delay(1);
}

static void i2c_start(void)
{
    GPIOA->BSRR = PIN_SDA; i2c_delay();
    GPIOA->BSRR = PIN_SCL; i2c_delay();
    GPIOA->BRR  = PIN_SDA; i2c_delay();
    GPIOA->BRR  = PIN_SCL; i2c_delay();
}

static void i2c_stop(void)
{
    GPIOA->BRR  = PIN_SDA; i2c_delay();
    GPIOA->BSRR = PIN_SCL; i2c_delay();
    GPIOA->BSRR = PIN_SDA; i2c_delay();
}

static int i2c_write_byte(uint8_t b)
{
    for (int i = 7; i >= 0; i--) {
        if (b & (1 << i)) GPIOA->BSRR = PIN_SDA; else GPIOA->BRR = PIN_SDA;
        i2c_delay();
        GPIOA->BSRR = PIN_SCL; i2c_delay();
        GPIOA->BRR  = PIN_SCL; i2c_delay();
    }
    /* Read ACK */
    GPIOA->BSRR = PIN_SDA; /* release */
    i2c_delay();
    GPIOA->BSRR = PIN_SCL; i2c_delay();
    int ack = (GPIOA->IDR & PIN_SDA) ? 1 : 0;
    GPIOA->BRR = PIN_SCL; i2c_delay();
    return ack; /* 0=ACK, 1=NACK */
}

static uint8_t i2c_read_byte(int send_ack)
{
    uint8_t val = 0;
    GPIOA->BSRR = PIN_SDA; /* release SDA for input */
    for (int i = 7; i >= 0; i--) {
        i2c_delay();
        GPIOA->BSRR = PIN_SCL; i2c_delay();
        if (GPIOA->IDR & PIN_SDA) val |= (1 << i);
        GPIOA->BRR = PIN_SCL; i2c_delay();
    }
    /* Send ACK/NACK */
    if (send_ack) GPIOA->BRR = PIN_SDA; else GPIOA->BSRR = PIN_SDA;
    i2c_delay();
    GPIOA->BSRR = PIN_SCL; i2c_delay();
    GPIOA->BRR  = PIN_SCL; i2c_delay();
    GPIOA->BSRR = PIN_SDA;
    return val;
}

static int i2c_read_reg(uint8_t dev_addr, uint8_t reg, uint8_t *val)
{
    i2c_start();
    if (i2c_write_byte(dev_addr << 1)) { i2c_stop(); return -1; } /* NACK */
    if (i2c_write_byte(reg))           { i2c_stop(); return -2; }
    i2c_start(); /* repeated start */
    if (i2c_write_byte((dev_addr << 1) | 1)) { i2c_stop(); return -3; }
    *val = i2c_read_byte(0); /* NACK after last byte */
    i2c_stop();
    return 0;
}

/* ── Main ────────────────────────────────────────────────────────────── */

int main(void)
{
    system_clock_init();
    led_gpio_init();
    usb_init();

    HAL_GPIO_WritePin(LED_SYS_PORT, LED_SYS_PIN, GPIO_PIN_SET);
    while (!tud_cdc_connected()) { tud_task(); }
    HAL_Delay(200);

    cdc_print("=== IMU I2C Probe (CS=HIGH) ===\r\n");

    i2c_gpio_init();
    HAL_Delay(100);

    /* Scan I2C addresses 0x00-0x7F */
    cdc_print("I2C bus scan:\r\n");
    int found = 0;
    for (uint8_t addr = 0x08; addr < 0x78; addr++) {
        i2c_start();
        int ack = i2c_write_byte(addr << 1);
        i2c_stop();
        HAL_Delay(1);
        if (ack == 0) {
            snprintf(pbuf, sizeof(pbuf), "  ACK at 0x%02X\r\n", addr);
            cdc_print(pbuf);
            found++;
        }
    }
    if (!found) cdc_print("  No devices found\r\n");

    /* Read WHO_AM_I from 0x6A at multiple possible register addresses */
    uint8_t val = 0;
    uint8_t who_regs[] = {0x0F, 0x00, 0x01, 0x75, 0x76};
    for (int i = 0; i < 5; i++) {
        int rc = i2c_read_reg(0x6A, who_regs[i], &val);
        snprintf(pbuf, sizeof(pbuf), "I2C 0x6A REG[0x%02X] = 0x%02X (rc=%d)\r\n", who_regs[i], val, rc);
        cdc_print(pbuf);
    }
    /* Dump first 32 registers */
    cdc_print("Reg dump 0x6A:\r\n");
    for (int r = 0; r < 0x80; r += 8) {
        snprintf(pbuf, sizeof(pbuf), "  0x%02X:", r);
        cdc_print(pbuf);
        for (int j = 0; j < 8; j++) {
            i2c_read_reg(0x6A, r + j, &val);
            snprintf(pbuf, sizeof(pbuf), " %02X", val);
            cdc_print(pbuf);
        }
        cdc_print("\r\n");
    }

    /* ── Configure QMI8658C at I2C 0x6A ────────────────────────────── */
    cdc_print("\r\nChip is QMI8658C (WHO_AM_I=0x05 at reg 0x00)\r\n");
    cdc_print("Configuring QMI8658C...\r\n");

    #define i2c_write_reg(addr, reg, v) do { \
        i2c_start(); \
        i2c_write_byte((addr) << 1); \
        i2c_write_byte(reg); \
        i2c_write_byte(v); \
        i2c_stop(); \
        HAL_Delay(1); \
    } while(0)

    #define QMI_ADDR  0x6A
    #define QMI_CTRL1 0x02
    #define QMI_CTRL2 0x03  /* Accel config: [7:4]=self-test, [3:0]= ODR+range */
    #define QMI_CTRL3 0x04  /* Gyro config */
    #define QMI_CTRL5 0x06  /* Low-pass filter */
    #define QMI_CTRL7 0x08  /* Enable: bit0=accel, bit1=gyro */

    /* CTRL2: Accel ±2g (bits[6:4]=000), ODR 1kHz (bits[3:0]=0x07) */
    i2c_write_reg(QMI_ADDR, QMI_CTRL2, 0x07);
    /* CTRL3: Gyro ±256dps (bits[6:4]=010), ODR 1kHz (bits[3:0]=0x07) */
    i2c_write_reg(QMI_ADDR, QMI_CTRL3, 0x27);
    /* CTRL7: Enable accel (bit0) + gyro (bit1) */
    i2c_write_reg(QMI_ADDR, QMI_CTRL7, 0x03);
    HAL_Delay(50);

    /* Verify */
    i2c_read_reg(QMI_ADDR, QMI_CTRL7, &val);
    snprintf(pbuf, sizeof(pbuf), "CTRL7 readback: 0x%02X (expect 0x03)\r\n", val);
    cdc_print(pbuf);

    cdc_print("=== Streaming (QMI8658 regs 0x35-0x40) ===\r\n");

    uint32_t last = 0;
    bool state = false;
    while (1) {
        tud_task();
        uint32_t now = HAL_GetTick();
        if (now - last >= 200) {
            last = now;
            state = !state;
            HAL_GPIO_WritePin(LED_SYS_PORT, LED_SYS_PIN, state ? GPIO_PIN_SET : GPIO_PIN_RESET);

            /* QMI8658 data: accel 0x35-0x3A, gyro 0x3B-0x40 (little-endian!) */
            uint8_t raw[12];
            for (int i = 0; i < 12; i++)
                i2c_read_reg(QMI_ADDR, 0x35 + i, &raw[i]);

            /* QMI8658 is LITTLE-endian (low byte first) */
            int16_t ax = (int16_t)(raw[1]<<8 | raw[0]);
            int16_t ay = (int16_t)(raw[3]<<8 | raw[2]);
            int16_t az = (int16_t)(raw[5]<<8 | raw[4]);
            int16_t gx = (int16_t)(raw[7]<<8 | raw[6]);
            int16_t gy = (int16_t)(raw[9]<<8 | raw[8]);
            int16_t gz = (int16_t)(raw[11]<<8 | raw[10]);

            snprintf(pbuf, sizeof(pbuf),
                     "ax=%6d ay=%6d az=%6d gx=%6d gy=%6d gz=%6d\r\n",
                     ax, ay, az, gx, gy, gz);
            cdc_print(pbuf);
        }
    }
}

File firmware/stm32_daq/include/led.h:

/**
 * led.h — LED_REC (PB4) and LED_SYS (PB5) control
 */

#ifndef LED_H
#define LED_H

#include <stdbool.h>

void led_init(void);

void led_rec_set(bool on);
void led_rec_toggle(void);

void led_sys_set(bool on);
void led_sys_toggle(void);

#endif /* LED_H */

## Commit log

2026-04-30 Initial commit: skill-capture-glove (ME740, BU 2026)
